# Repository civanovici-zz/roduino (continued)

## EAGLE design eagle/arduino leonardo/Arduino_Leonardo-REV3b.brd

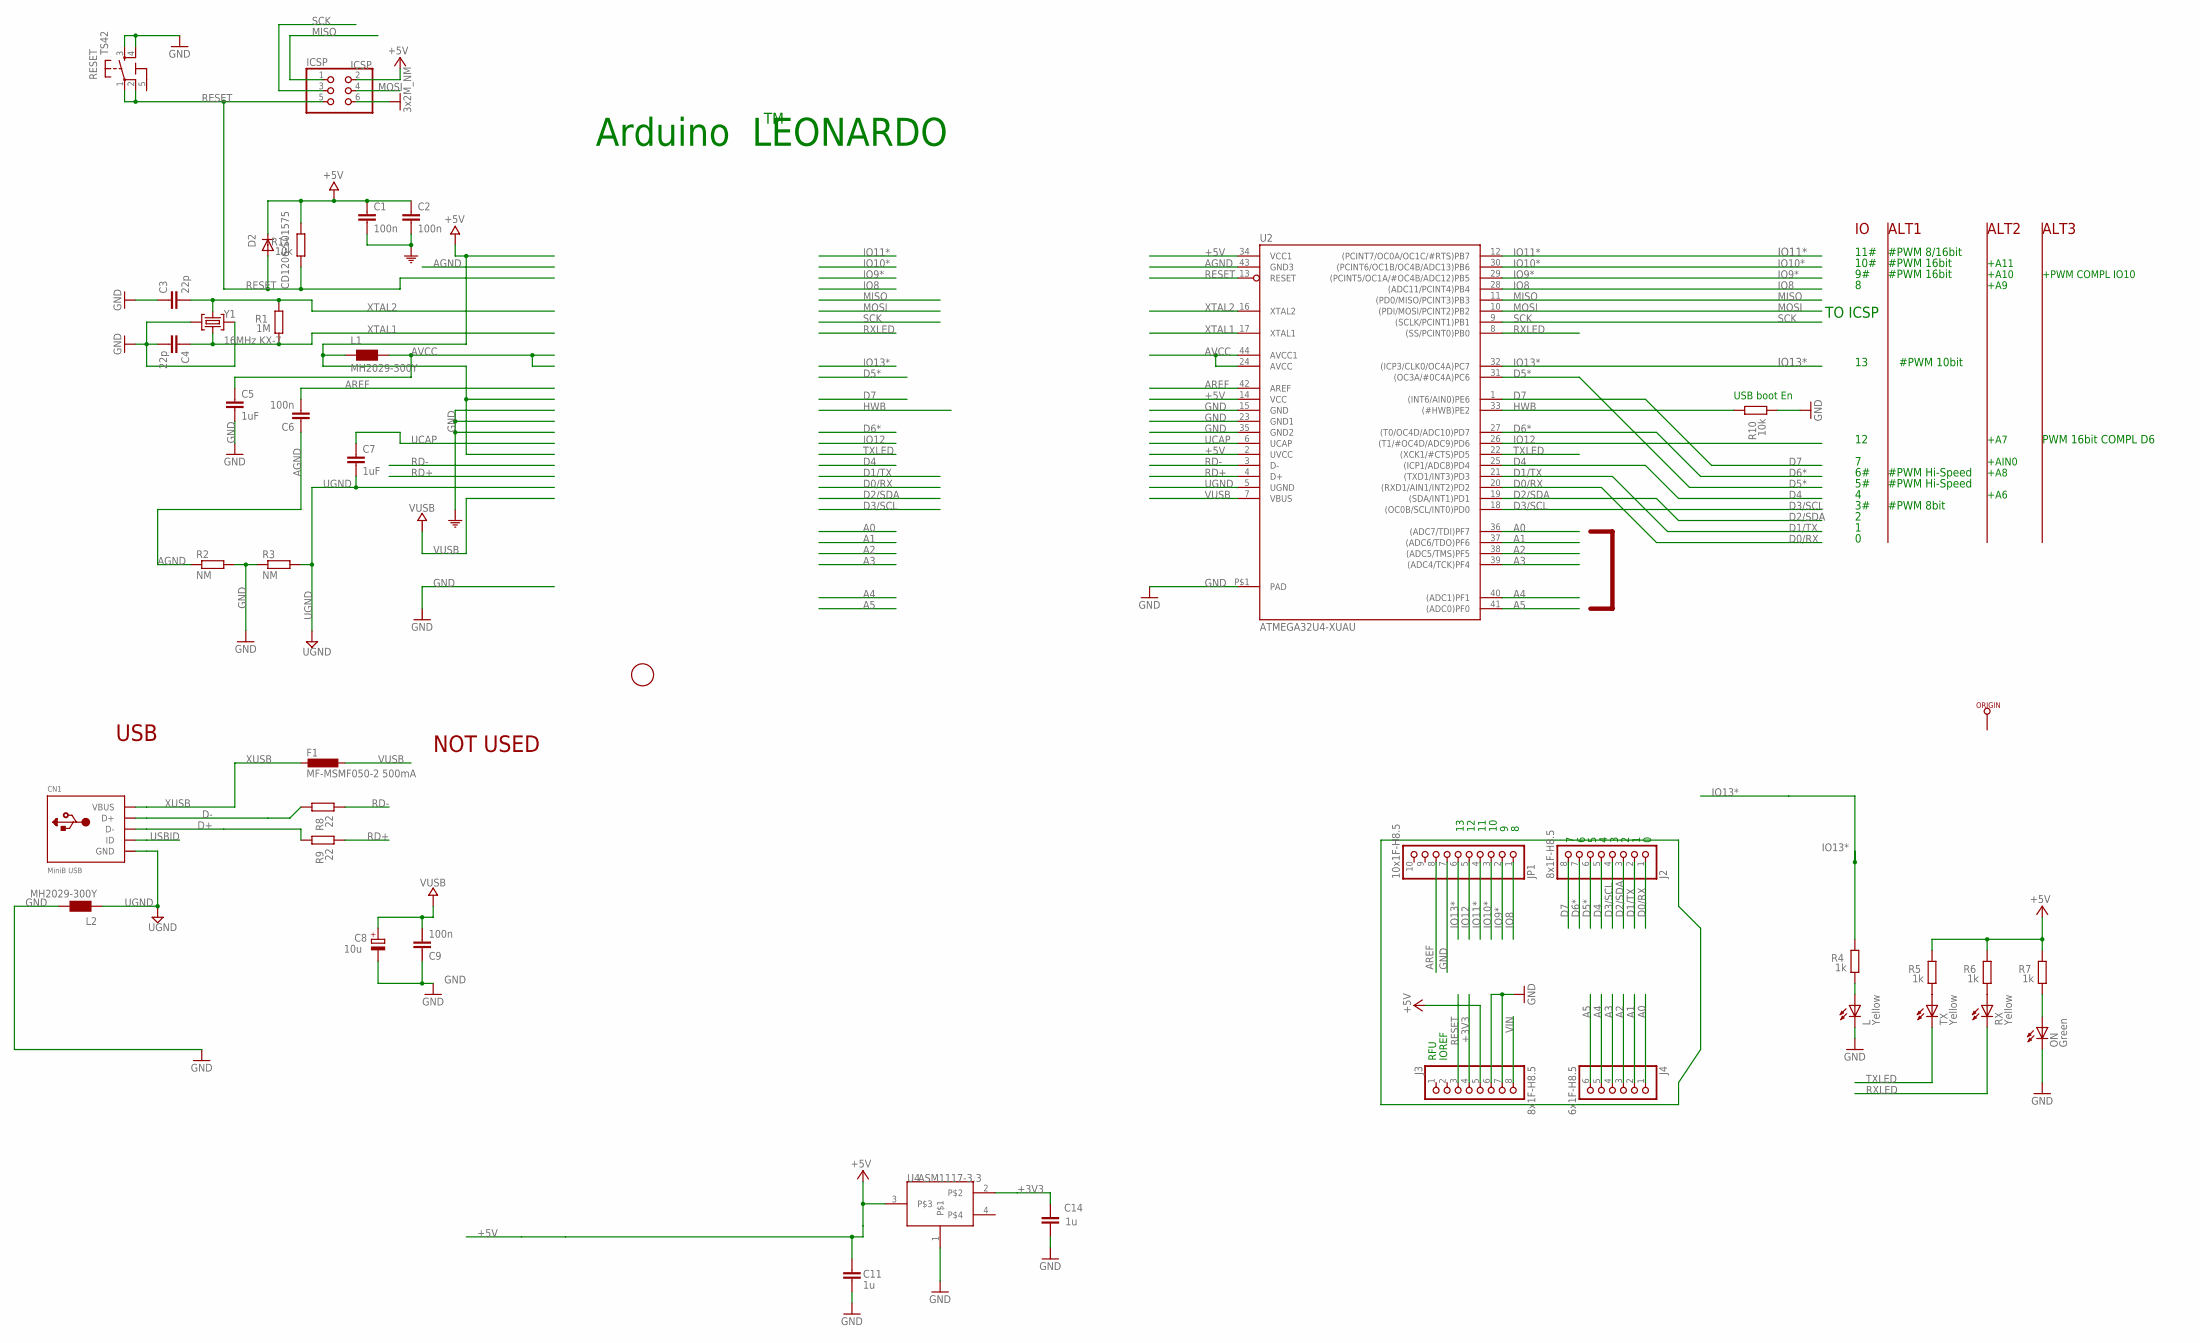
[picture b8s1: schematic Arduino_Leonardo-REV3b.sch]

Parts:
C1, C2, C6, C9: 100n; C0805
C3, C4: 22p; C0805
C5, C7: 1uF; C0805
C8: 10u; SMC_B
C11, C14: 1u; C0805
CN1: MiniB USB; USB-MINIB
D2: CD1206-S01575; MINIMELF
F1: MF-MSMF050-2 500mA; L1812
FID1: FIDUCIALMOUNT; FIDUCIA-MOUNT
ICSP: ICSP; 2X03
J2, J3: 8x1F-H8.5; 1X08
J4: 6x1F-H8.5; 1X06
JP1: 10x1F-H8.5; 1X10
L: Yellow; CHIPLED_0805
L1, L2: MH2029-300Y; 0805
ON: Green; CHIPLED_0805
ORIGIN: TP_SP; TP-SP
R1: 1M; R0805
R2, R3: NM; R0805
R4, R5, R6, R7: 1k; R0805
R8, R9: 22; R0805
R10, R11: 10k; R0805
RESET: TS42
RX: Yellow; CHIPLED_0805
TX: Yellow; CHIPLED_0805
U2: ATMEGA32U4-XUAU; TQFP44-PAD
U4: ASM1117-3.3; SOT223
Y1: 16MHz KX-7; CRYSTAL-3.2-2.5

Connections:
5-GND: RESET.5 (5-GND)
+3V3: C14.2, J3.4, U4.2
+5V: C1.1, C2.1, C11.2, D2.C, ICSP.2, J3.5, L1.1, R5.2, R6.2, R7.2, R11.2, U2.2 (UVCC), U2.14 (VCC), U2.34 (VCC1), U4.3
A0: J4.1, U2.36 ((ADC7/TDI)PF7)
A1: J4.2, U2.37 ((ADC6/TDO)PF6)
A2: J4.3, U2.38 ((ADC5/TMS)PF5)
A3: J4.4, U2.39 ((ADC4/TCK)PF4)
A4: J4.5, U2.40 ((ADC1)PF1)
A5: J4.6, U2.41 ((ADC0)PF0)
AGND: C6.1, R2.1, U2.43 (GND3)
AREF: C6.2, JP1.8, U2.42 (AREF)
AVCC: C5.1, L1.2, U2.24 (AVCC), U2.44 (AVCC1)
D0/RX: J2.1, U2.20 ((RXD1/AIN1/INT2)PD2)
D1/TX: J2.2, U2.21 ((TXD1/INT3)PD3)
D2/SDA: J2.3, U2.19 ((SDA/INT1)PD1)
D3/SCL: J2.4, U2.18 ((OC0B/SCL/INT0)PD0)
D4: J2.5, U2.25 ((ICP1/ADC8)PD4)
D5*: J2.6, U2.31 ((OC3A/#0C4A)PC6)
D6*: J2.7, U2.27 ((T0/OC4D/ADC10)PD7)
D7: J2.8, U2.1 ((INT6/AIN0)PE6)
D+: CN1.D-, R9.2
D-: CN1.D+, R8.2
GND: C1.2, C2.2, C3.1, C4.2, C5.2, C8.-, C9.1, C11.1, C14.1, ICSP.6, J3.6, J3.7, JP1.7, L.C, L2.2, ON.C, R2.2, R3.1, R10.1, RESET.3, RESET.4, U2.15 (GND), U2.23 (GND1), U2.35 (GND2), U2.P$1 (PAD), U4.1, Y1.2 (GND), Y1.4 (GND)
HWB: R10.2, U2.33 ((#HWB)PE2)
IO8: JP1.1, U2.28 ((ADC11/PCINT4)PB4)
IO9*: JP1.2, U2.29 ((PCINT5/OC1A/#OC4B/ADC12)PB5)
IO10*: JP1.3, U2.30 ((PCINT6/OC1B/OC4B/ADC13)PB6)
IO11*: JP1.4, U2.12 ((PCINT7/OC0A/OC1C/#RTS)PB7)
IO12: JP1.5, U2.26 ((T1/#OC4D/ADC9)PD6)
IO13*: JP1.6, R4.2, U2.32 ((ICP3/CLK0/OC4A)PC7)
MISO: ICSP.1, U2.11 ((PD0/MISO/PCINT3)PB3)
MOSI: ICSP.4, U2.10 ((PDI/MOSI/PCINT2)PB2)
unnamed: R5.1, TX.A
unnamed: L.A, R4.1
unnamed: ON.A, R7.1
unnamed: R6.1, RX.A
RD+: R9.1, U2.4 (D+)
RD-: R8.1, U2.3 (D-)
RESET: D2.A, ICSP.5, J3.3, R11.1, RESET.1, RESET.2, U2.13 (RESET)
RXLED: RX.C, U2.8 ((SS/PCINT0)PB0)
SCK: ICSP.3, U2.9 ((SCLK/PCINT1)PB1)
TXLED: TX.C, U2.22 ((XCK1/#CTS)PD5)
UCAP: C7.1, U2.6 (UCAP)
UGND: C7.2, CN1.GND, L2.1, R3.2, U2.5 (UGND)
USBID: CN1.ID
VIN: J3.8
VUSB: C8.+, C9.2, F1.1, U2.7 (VBUS)
XTAL1: C4.1, R1.1, U2.17 (XTAL1), Y1.1 (C1)
XTAL2: C3.2, R1.2, U2.16 (XTAL2), Y1.3 (C2)
XUSB: CN1.VBUS, F1.2

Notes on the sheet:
Arduino LEONARDO
USB boot En
USB
NOT USED
TO ICSP
10#
11#
#PWM 8bit
#PWM Hi-Speed
#PWM 8/16bit
#PWM 16bit
PWM 16bit COMPL D6
#PWM 10bit
+A6
+A7
IOREF
RFU
+A11
+A10
+A8
+A9
+PWM COMPL IO10
+AIN0
ALT1
ALT2
ALT3

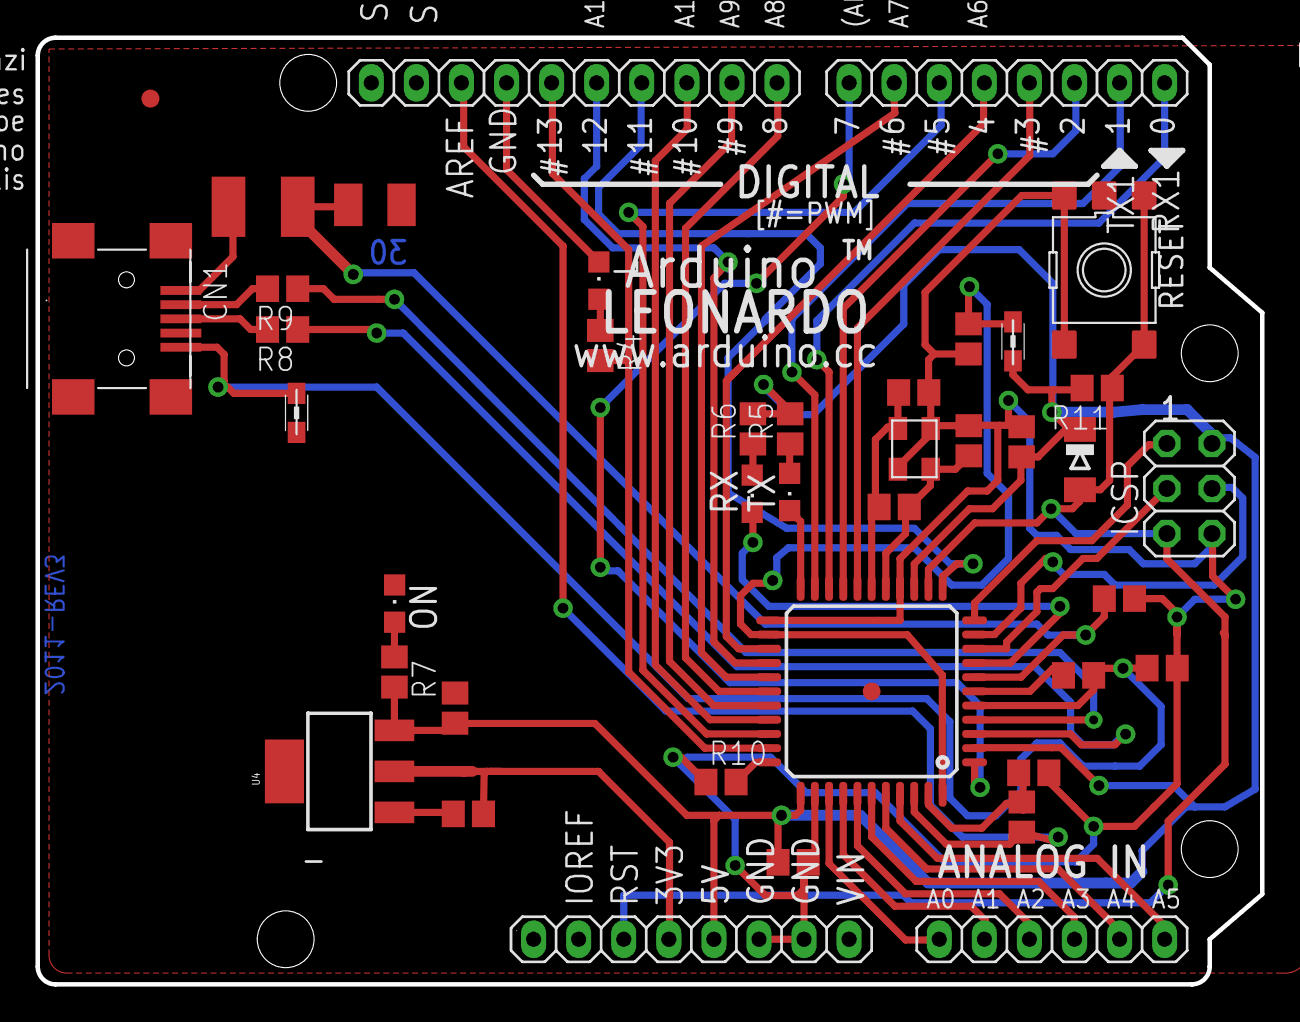
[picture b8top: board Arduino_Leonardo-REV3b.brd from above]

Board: 2 copper layers, 69.0 x 53.3 mm, 42 parts (0 on the bottom side), 47 nets.

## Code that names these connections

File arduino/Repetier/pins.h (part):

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*
*                  ATMega168
*                   +-\/-+
*             PC6  1|    |28  PC5 (AI 5 / D19)
*       (D 0) PD0  2|    |27  PC4 (AI 4 / D18)
*       (D 1) PD1  3|    |26  PC3 (AI 3 / D17)
*       (D 2) PD2  4|    |25  PC2 (AI 2 / D16)
*  PWM+ (D 3) PD3  5|    |24  PC1 (AI 1 / D15)
*       (D 4) PD4  6|    |23  PC0 (AI 0 / D14)
*             VCC  7|    |22  GND
*             GND  8|    |21  AREF
*             PB6  9|    |20  AVCC
*             PB7 10|    |19  PB5 (D 13)
*  PWM+ (D 5) PD5 11|    |18  PB4 (D 12)
*  PWM+ (D 6) PD6 12|    |17  PB3 (D 11) PWM
*       (D 7) PD7 13|    |16  PB2 (D 10) PWM
*       (D 8) PB0 14|    |15  PB1 (D 9)  PWM
*                   +----+
****************************************************************************************/
#if MOTHERBOARD == 0
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*                        ATMega644P
*
*                        +---\/---+
*            (D 0) PB0  1|        |40  PA0 (AI 0 / D31)
*            (D 1) PB1  2|        |39  PA1 (AI 1 / D30)
*       INT2 (D 2) PB2  3|        |38  PA2 (AI 2 / D29)
*        PWM (D 3) PB3  4|        |37  PA3 (AI 3 / D28)
*        PWM (D 4) PB4  5|        |36  PA4 (AI 4 / D27)
*       MOSI (D 5) PB5  6|        |35  PA5 (AI 5 / D26)
*       MISO (D 6) PB6  7|        |34  PA6 (AI 6 / D25)
*        SCK (D 7) PB7  8|        |33  PA7 (AI 7 / D24)
*                  RST  9|        |32  AREF
*                  VCC 10|        |31  GND 
*                  GND 11|        |30  AVCC
*                XTAL2 12|        |29  PC7 (D 23)
*                XTAL1 13|        |28  PC6 (D 22)
*       RX0 (D 8)  PD0 14|        |27  PC5 (D 21) TDI
*       TX0 (D 9)  PD1 15|        |26  PC4 (D 20) TDO
*  INT0 RX1 (D 10) PD2 16|        |25  PC3 (D 19) TMS
*  INT1 TX1 (D 11) PD3 17|        |24  PC2 (D 18) TCK
*       PWM (D 12) PD4 18|        |23  PC1 (D 17) SDA
*       PWM (D 13) PD5 19|        |22  PC0 (D 16) SCL
*       PWM (D 14) PD6 20|        |21  PD7 (D 15) PWM
*                        +--------+
*
****************************************************************************************/
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
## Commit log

2013-02-27 Elecronic adventures
